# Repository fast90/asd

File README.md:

#Audio Switch Daemon

This circuit switches two audio sources, based on the status of a MPD-server running on a Raspberry Pi.

If MPD is playing the Raspberry Pi (INPUT 2) is switched to OUT.
When MPD stops playing OUT is switched back to INPUT 1.

# Library
Libbcm2835 is used for GPIO access. See http://www.airspayce.com/mikem/bcm2835/ for details.

# Schematic

# Wiring
| Raspberry Pi Pin No. | Audioswitch Pin | Function |
|:--------------------:|:---------------:|:--------:|
| 8                    | SV2 - 3         | GPIO 14  |
| 2                    | SV2 - 2         | GND      |
| 6                    | SV2 - 1         | +5V      |

SV1 can be used to connect a manual switch.

# Setup
Install the Library see http://www.airspayce.com/mikem/bcm2835/ for details.

If you are using a Raspberry Pi 2 you need to enable device tree support!

```bash
sudo raspi-config
```
```bash
->Advanced Options -> enable Device Tree
sudo shutdown -r now
```
Then type
```bash
./configure
make
make install
```

# Configuration & Usage
|  Option   |   Argument   |          Function        |       Default      |
|:---------:|:------------:|:------------------------:|:-------------------|
|  h        |              |Show help                 |                    |
|  v        |              |Show version              |                    |
| no-daemon |              |Don't detach from console |                    |
|  p        | <PinNumber>  |Change Pin                | GPIO17             |
|  s        | <SocketPath> |Change Path to socket     |/home/pi/.mpd/socket|

```bash
asd -p 17 -s /home/user/.mpd/sock
```

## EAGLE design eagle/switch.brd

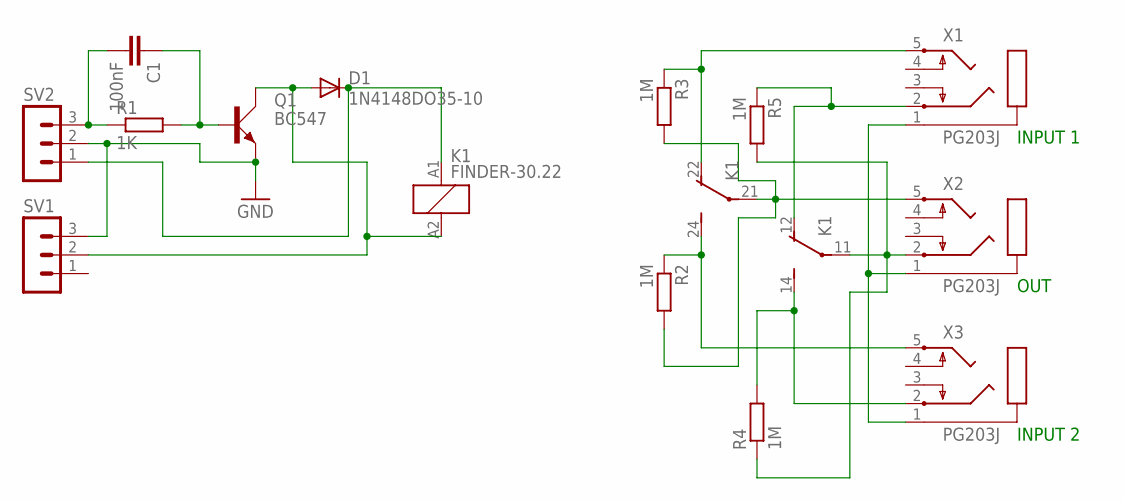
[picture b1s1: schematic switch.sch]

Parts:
C1: 100nF; C025-025X050
D1: 1N4148DO35-10; DO35-10
K1: FINDER-30.22
Q1: BC547; SOT54A
R1: 1K; 0207/10
R2, R3, R4, R5: 1M; 0207/10
SV1, SV2: MA03-1
X1, X2, X3: PG203J

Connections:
GND: Q1.E, SV1.3, SV2.2
unnamed: K1.22 (O), R3.1, X1.5
unnamed: K1.24 (S), R2.1, X3.5
unnamed: K1.11, R4.1, R5.2, X2.2
unnamed: D1.A, K1.A2 (2), Q1.C, SV1.2
unnamed: K1.12 (O), R5.1, X1.2
unnamed: K1.14 (S), R4.2, X3.2
unnamed: C1.2, R1.1, SV2.3
unnamed: C1.1, Q1.B, R1.2
unnamed: X1.1, X2.1, X3.1
unnamed: D1.C, K1.A1 (1), SV2.1
unnamed: K1.21, R2.2, R3.2, X2.5

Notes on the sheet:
OUT
INPUT 1
INPUT 2

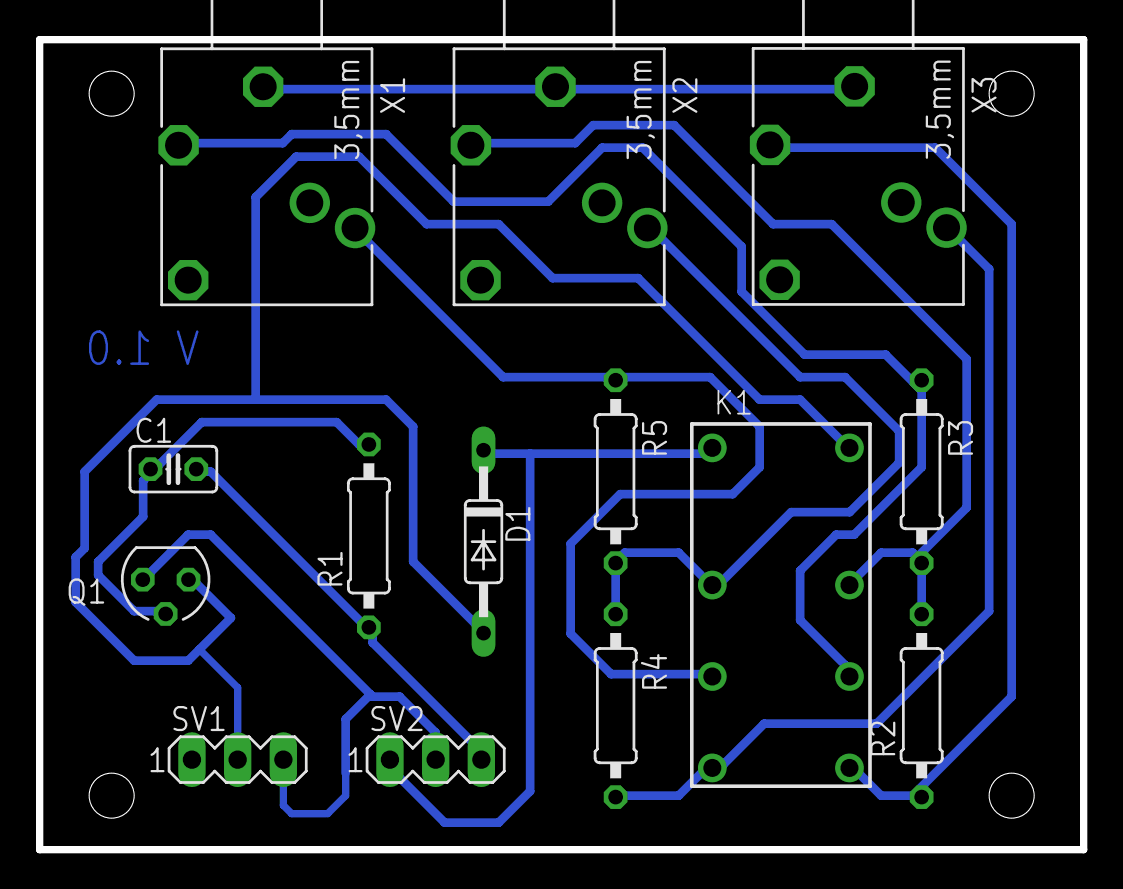
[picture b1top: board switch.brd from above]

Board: 2 copper layers, 58.0 x 45.0 mm, 14 parts (0 on the bottom side), 12 nets.
